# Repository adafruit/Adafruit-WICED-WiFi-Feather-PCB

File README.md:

## Adafruit WICED WiFi Feather PCB
<a href="http://www.adafruit.com/products/3056"><br/>
Click here to purchase one from the Adafruit shop</a>

The WICED Feather is based on Cypress (formerly Broadcom) WICED (Wireless Internet Connectivity for Embedded Devices) platform, and is paired up with a powerful STM32F205 ARM Cortex M3 processor running at 120MHz, with support for TLS 1.2 to access sites and web services safely and securely.

PCB files for the Adafruit WICED WiFi Feather. The format is EagleCAD schematic and board layout
- https://www.adafruit.com/product/3056

### License

Adafruit invests time and resources providing this open source design, please support Adafruit and open-source hardware by purchasing products from [Adafruit](https://www.adafruit.com)!

All text above must be included in any redistribution

Designed by Limor Fried/Ladyada for Adafruit Industries.
Creative Commons Attribution/Share-Alike, all text above must be included in any redistribution. 
See license.txt for additional information.

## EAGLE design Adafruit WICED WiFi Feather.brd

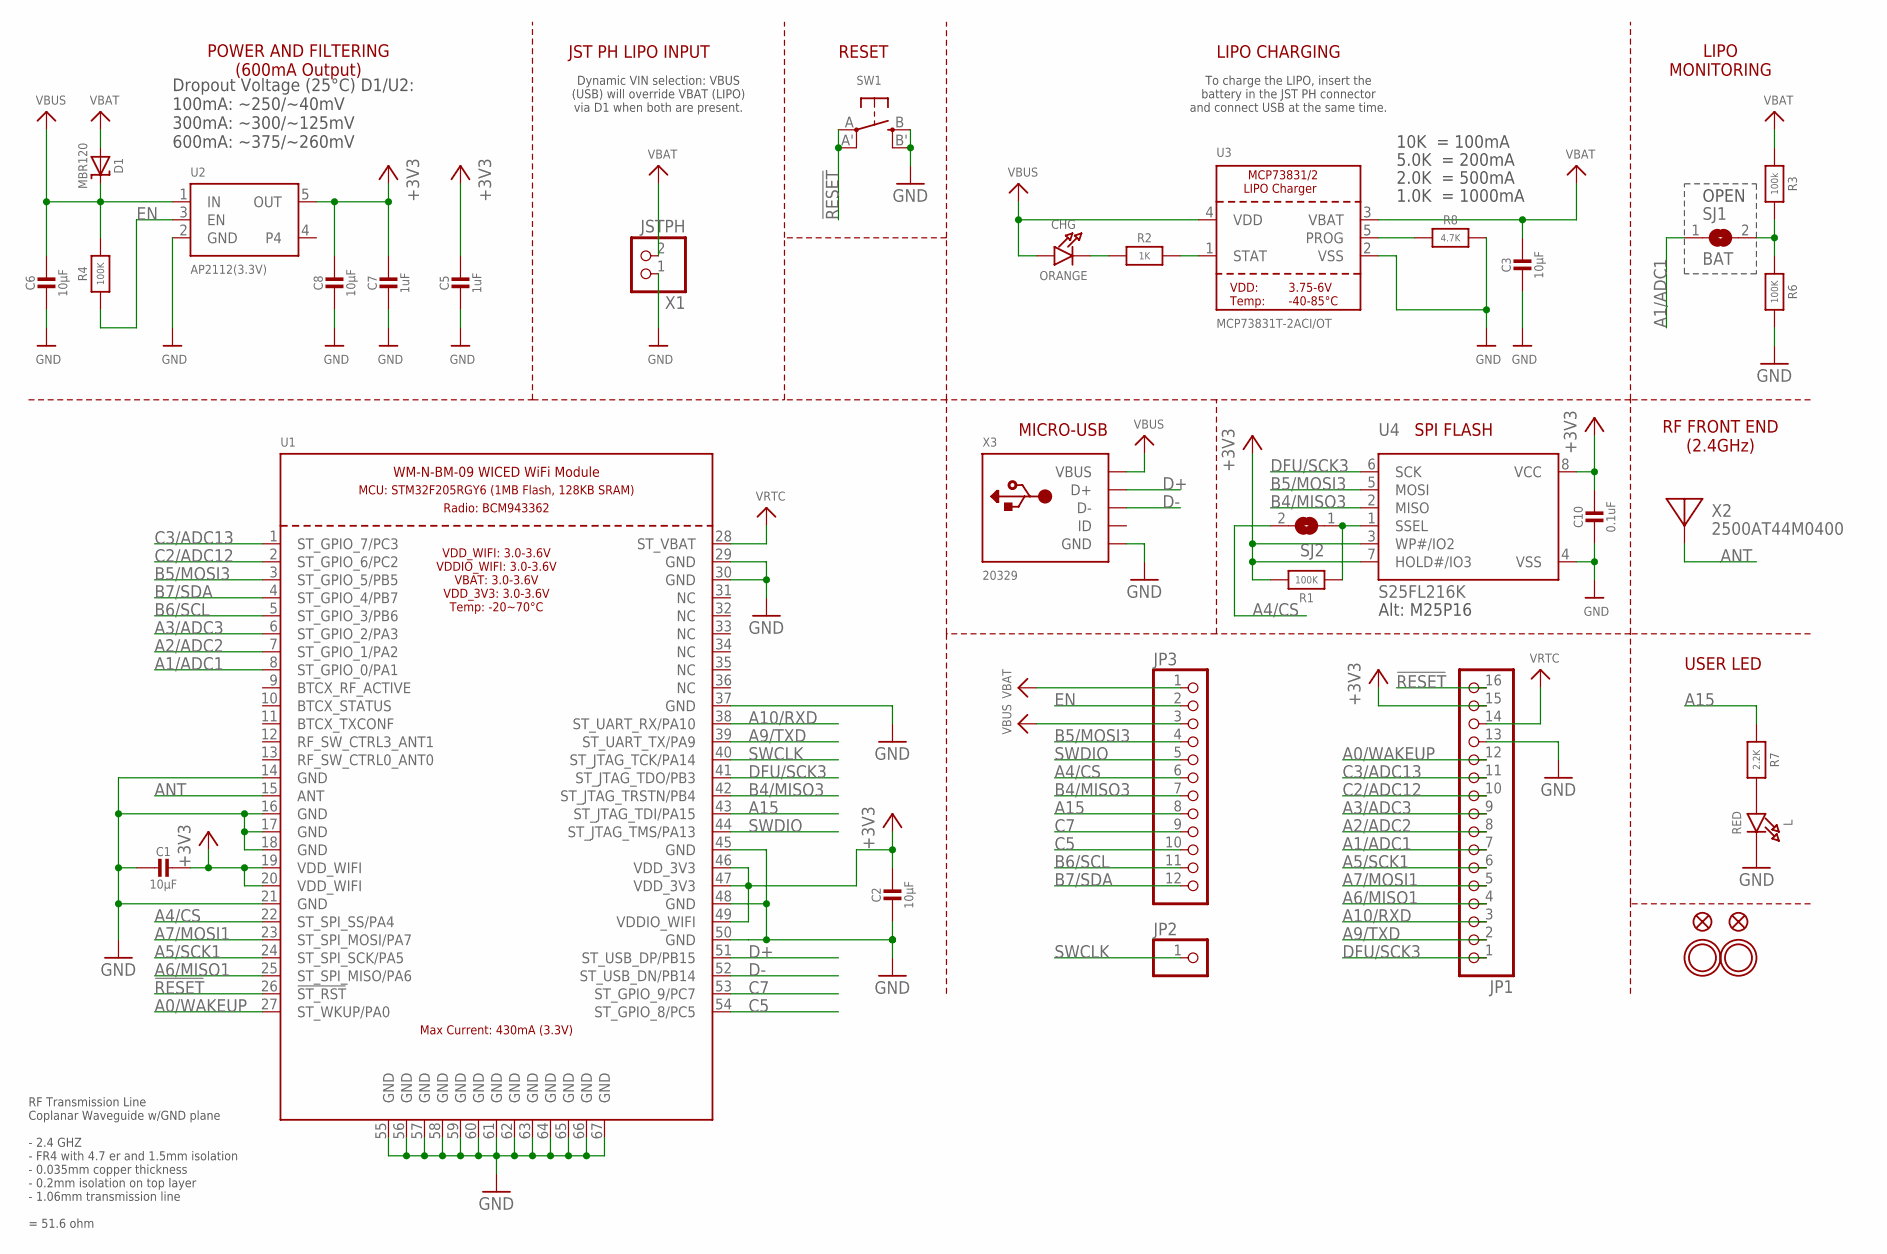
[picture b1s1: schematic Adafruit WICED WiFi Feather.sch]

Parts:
C1, C2, C3, C6, C8: 10µF; 0805-NO
C5, C7: 1uF; 0603-NO
C10: 0.1uF; 0805_10MGAP
CHG: ORANGE; CHIPLED_0805_NOOUTLINE
D1: MBR120; SOD-123
JP1: HEADER-1X16ROUND; 1X16_ROUND
JP2: HEADER-1X1ROUND; 1X01_ROUND
JP3: HEADER-1X12; 1X12_ROUND
L: RED; CHIPLED_0805_NOOUTLINE
R1, R4, R6: 100K; 0603-NO
R2: 1K; 0603-NO
R3: 100k; 0603-NO
R7: 2.2K; 0603-NO
R8: 4.7K; 0603-NO
SJ1: BAT; SOLDERJUMPER_REFLOW_NOPASTE
SJ2: SOLDERJUMPER; SOLDERJUMPER_ARROW_NOPASTE
SW1: SWITCH_TACT_SMT4.6X2.8; BTN_KMR2_4.6X2.8
U1: USI_WM-N-BM-09
U2: AP2112(3.3V); SOT23-5
U3: MCP73831T-2ACI/OT; SOT23-5
U4: S25FL216K; SOIC8_150MIL
U$31, U$32: MOUNTINGHOLE2.5; MOUNTINGHOLE_2.5_PLATED
U$34, U$35: FIDUCIAL""; FIDUCIAL_1MM
X1: JSTPH; JSTPH2
X2: 2500AT44M0400; ANT_2500AT44M0400
X3: 20329; 4UCONN_20329_V2

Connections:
!RESET: JP1.16, SW1.A, SW1.A' (P1), U1.26 (!ST_RST)
+3V3: C1.1, C2.1, C5.1, C7.1, C8.1, C10.1, JP1.15, R1.2, U1.19 (VDD_WIFI), U1.20 (VDD_WIFI), U1.46 (VDD_3V3), U1.47 (VDD_3V3), U1.49 (VDDIO_WIFI), U2.5 (OUT), U4.3 (WP#/IO2), U4.7 (HOLD#/IO3), U4.8 (VCC)
A0/WAKEUP: JP1.12, U1.27 (ST_WKUP/PA0)
A1/ADC1: JP1.7, SJ1.1, U1.8 (ST_GPIO_0/PA1)
A2/ADC2: JP1.8, U1.7 (ST_GPIO_1/PA2)
A3/ADC3: JP1.9, U1.6 (ST_GPIO_2/PA3)
A4/CS: JP3.6, SJ2.2, U1.22 (ST_SPI_SS/PA4)
A5/SCK1: JP1.6, U1.24 (ST_SPI_SCK/PA5)
A6/MISO1: JP1.4, U1.25 (ST_SPI_MISO/PA6)
A7/MOSI1: JP1.5, U1.23 (ST_SPI_MOSI/PA7)
A9/TXD: JP1.2, U1.39 (ST_UART_TX/PA9)
A10/RXD: JP1.3, U1.38 (ST_UART_RX/PA10)
A15: JP3.8, R7.1, U1.43 (ST_JTAG_TDI/PA15)
ANT: U1.15 (ANT), X2.FEED
B4/MISO3: JP3.7, U1.42 (ST_JTAG_TRSTN/PB4), U4.2 (MISO)
B5/MOSI3: JP3.4, U1.3 (ST_GPIO_5/PB5), U4.5 (MOSI)
B6/SCL: JP3.11, U1.5 (ST_GPIO_3/PB6)
B7/SDA: JP3.12, U1.4 (ST_GPIO_4/PB7)
C2/ADC12: JP1.10, U1.2 (ST_GPIO_6/PC2)
C3/ADC13: JP1.11, U1.1 (ST_GPIO_7/PC3)
C5: JP3.10, U1.54 (ST_GPIO_8/PC5)
C7: JP3.9, U1.53 (ST_GPIO_9/PC7)
D+: U1.51 (ST_USB_DP/PB15), X3.D+
D-: U1.52 (ST_USB_DN/PB14), X3.D-
DFU/SCK3: JP1.1, U1.41 (ST_JTAG_TDO/PB3), U4.6 (SCK)
EN: JP3.2, R4.1, U2.3 (EN)
GND: C1.2, C2.2, C3.2, C5.2, C6.2, C7.2, C8.2, C10.2, JP1.13, L.C, R6.2, R8.2, SW1.B (S), SW1.B' (S1), U1.14 (GND), U1.16 (GND), U1.17 (GND), U1.18 (GND), U1.21 (GND), U1.29 (GND), U1.30 (GND), U1.37 (GND), U1.45 (GND), U1.48 (GND), U1.50 (GND), U1.55 (GND), U1.56 (GND), U1.57 (GND), U1.58 (GND), U1.59 (GND), U1.60 (GND), U1.61 (GND), U1.62 (GND), U1.63 (GND), U1.64 (GND), U1.65 (GND), U1.66 (GND), U1.67 (GND), U2.2 (GND), U3.2 (VSS), U4.4 (VSS), X1.1, X3.BASE@1 (GND), X3.BASE@2 (GND), X3.GND, X3.SPRT@1 (GND), X3.SPRT@2 (GND), X3.SPRT@3 (GND), X3.SPRT@4 (GND)
unnamed: CHG.C, R2.1
unnamed: L.A, R7.2
unnamed: R2.2, U3.1 (STAT)
unnamed: R8.1, U3.5 (PROG)
unnamed: R3.2, R6.1, SJ1.2
unnamed: R1.1, SJ2.1, U4.1 (SSEL)
SWCLK: JP2.1, U1.40 (ST_JTAG_TCK/PA14)
SWDIO: JP3.5, U1.44 (ST_JTAG_TMS/PA13)
VBAT: C3.1, D1.A, JP3.1, R3.1, U3.3 (VBAT), X1.2
VBUS: C6.1, CHG.A, D1.C, JP3.3, R4.2, U2.1 (IN), U3.4 (VDD), X3.VBUS
VRTC: JP1.14, U1.28 (ST_VBAT)

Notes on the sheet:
POWER AND FILTERING (600mA Output)
RESET
10K = 100mA
5.0K = 200mA
2.0K = 500mA
1.0K = 1000mA
LIPO CHARGING
Alt: M25P16
MICRO-USB
SPI FLASH
USER LED
LIPO MONITORING
OPEN
RF FRONT END (2.4GHz)
JST PH LIPO INPUT
Dynamic VIN selection: VBUS (USB) will override VBAT (LIPO) via D1 when both are present.
To charge the LIPO, insert the battery in the JST PH connector and connect USB at the same time.
RF Transmission Line Coplanar Waveguide w/GND plane - 2.4 GHZ - FR4 with 4.7 er and 1.5mm isolation - 0.035mm copper thickness - 0.2mm isolation on top layer - 1.06mm transmission line = 51.6 ohm
Dropout Voltage (25°C) D1/U2: 100mA: ~250/~40mV 300mA: ~300/~125mV 600mA: ~375/~260mV

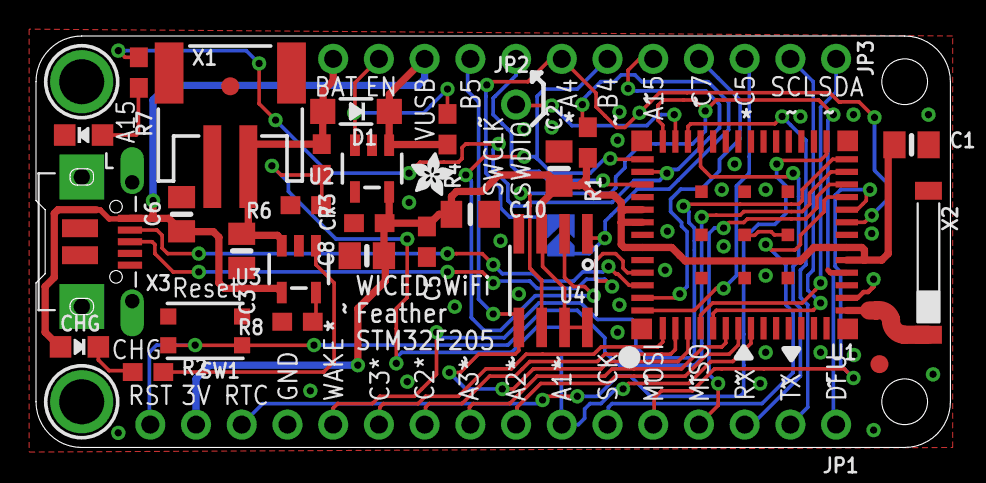
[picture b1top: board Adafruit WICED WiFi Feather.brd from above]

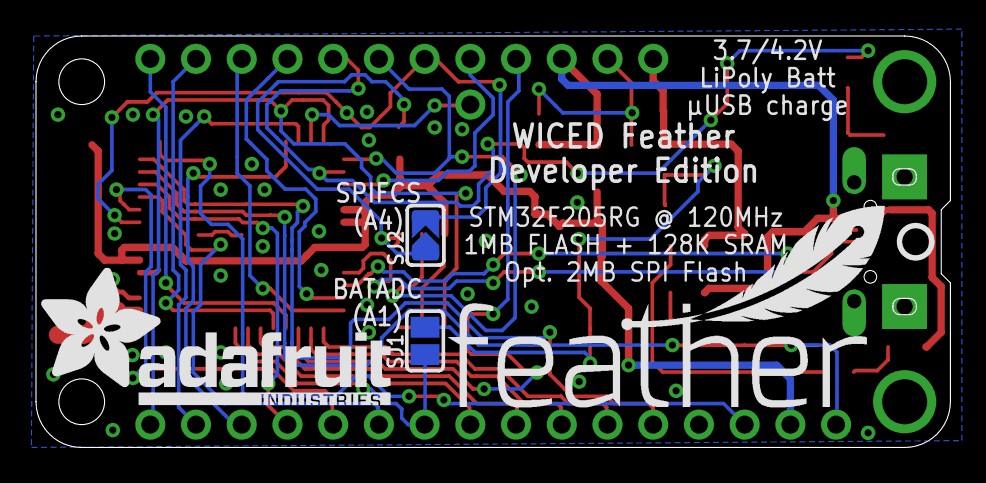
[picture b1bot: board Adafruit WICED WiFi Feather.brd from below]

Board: 2 copper layers, 50.8 x 22.9 mm, 39 parts (5 on the bottom side), 38 nets.

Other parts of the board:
U$7: FEATHERLOGO
U$8: ADAFRUIT_2.5MM
U$10: ADAFRUIT_TEXT_20MM
U$23: PCBFEAT-REV-040

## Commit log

2016-06-14 init

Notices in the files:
parts and their libraries:
microbuilder: This work is placed in the public domain, and may be freely used for commercial and non-commercial work with the following conditions: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
